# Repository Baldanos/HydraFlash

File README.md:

# Hydrabus NAND Flash shield

This shield uses the template made by Antti Nykänen <aon@umetronics.com>

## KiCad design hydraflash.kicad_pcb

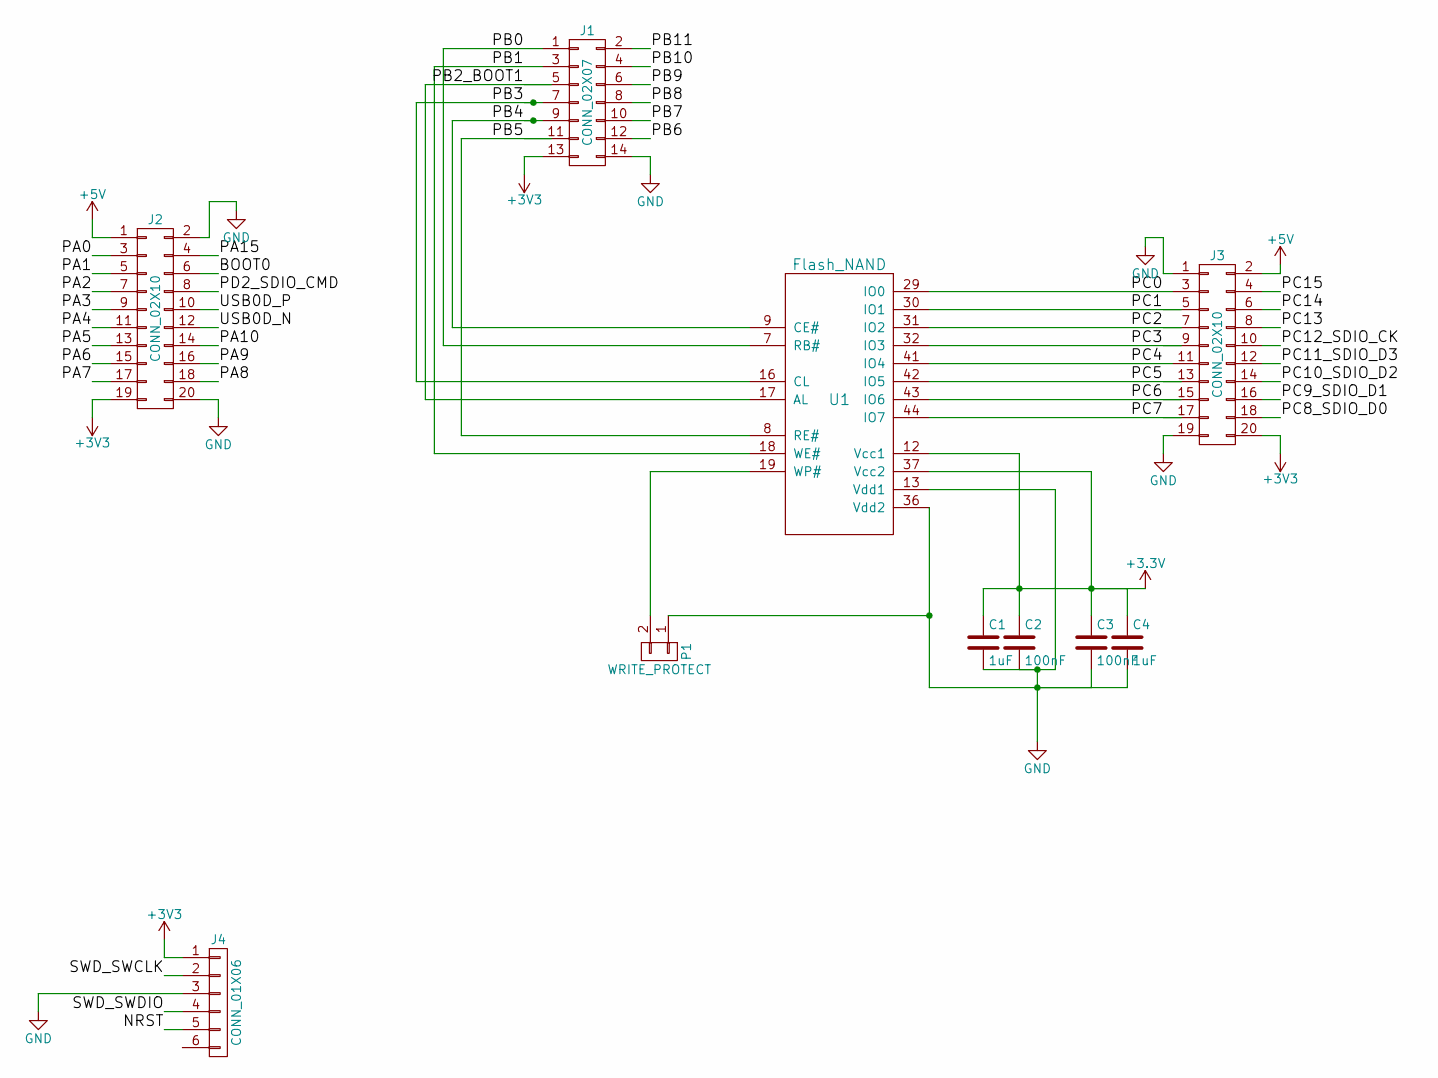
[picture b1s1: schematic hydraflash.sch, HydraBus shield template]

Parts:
C1, C4: 1uF; C_0805_HandSoldering
C2, C3: 100nF; C_0805_HandSoldering
J1: CONN_02X07; Hydrabus_Shield_Conn_2x07
J2, J3: CONN_02X10; Hydrabus_Shield_Conn_2x10
J4: CONN_01X06; Hydrabus_Shield_Conn_1x06
P1: WRITE_PROTECT; Pin_Header_Straight_1x02
U1: Flash_NAND; TSOP48ZIF

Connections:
+5V: J2.1, J3.2
/BOOT0: J2.6
/NRST: J4.5
/PA0: J2.3
/PA1: J2.5
/PA2: J2.7
/PA3: J2.9
/PA4: J2.11
/PA5: J2.13
/PA6: J2.15
/PA7: J2.17
/PA8: J2.18
/PA9: J2.16
/PA10: J2.14
/PA15: J2.4
/PB0: J1.1, U1.7 (RB#)
/PB1: J1.3, U1.18 (WE#)
/PB2_BOOT1: J1.5, U1.17 (AL)
/PB3: J1.7, U1.16 (CL)
/PB4: J1.9, U1.9 (CE#)
/PB5: J1.11, U1.8 (RE#)
/PB6: J1.12
/PB7: J1.10
/PB8: J1.8
/PB9: J1.6
/PB10: J1.4
/PB11: J1.2
/PC0: J3.3, U1.29 (IO0)
/PC1: J3.5, U1.30 (IO1)
/PC2: J3.7, U1.31 (IO2)
/PC3: J3.9, U1.32 (IO3)
/PC4: J3.11, U1.41 (IO4)
/PC5: J3.13, U1.42 (IO5)
/PC6: J3.15, U1.43 (IO6)
/PC7: J3.17, U1.44 (IO7)
/PC8_SDIO_D0: J3.18
/PC9_SDIO_D1: J3.16
/PC10_SDIO_D2: J3.14
/PC11_SDIO_D3: J3.12
/PC12_SDIO_CK: J3.10
/PC13: J3.8
/PC14: J3.6
/PC15: J3.4
/PD2_SDIO_CMD: J2.8
/SWD_SWCLK: J4.2
/SWD_SWDIO: J4.4
/USB0D_N: J2.12
/USB0D_P: J2.10
GND: C1.2, C2.2, C3.2, C4.2, J1.14, J2.2, J2.20, J3.1, J3.19, J4.3, P1.1, U1.13 (Vdd1), U1.36 (Vdd2)
unnamed: P1.2, U1.19 (WP#)

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
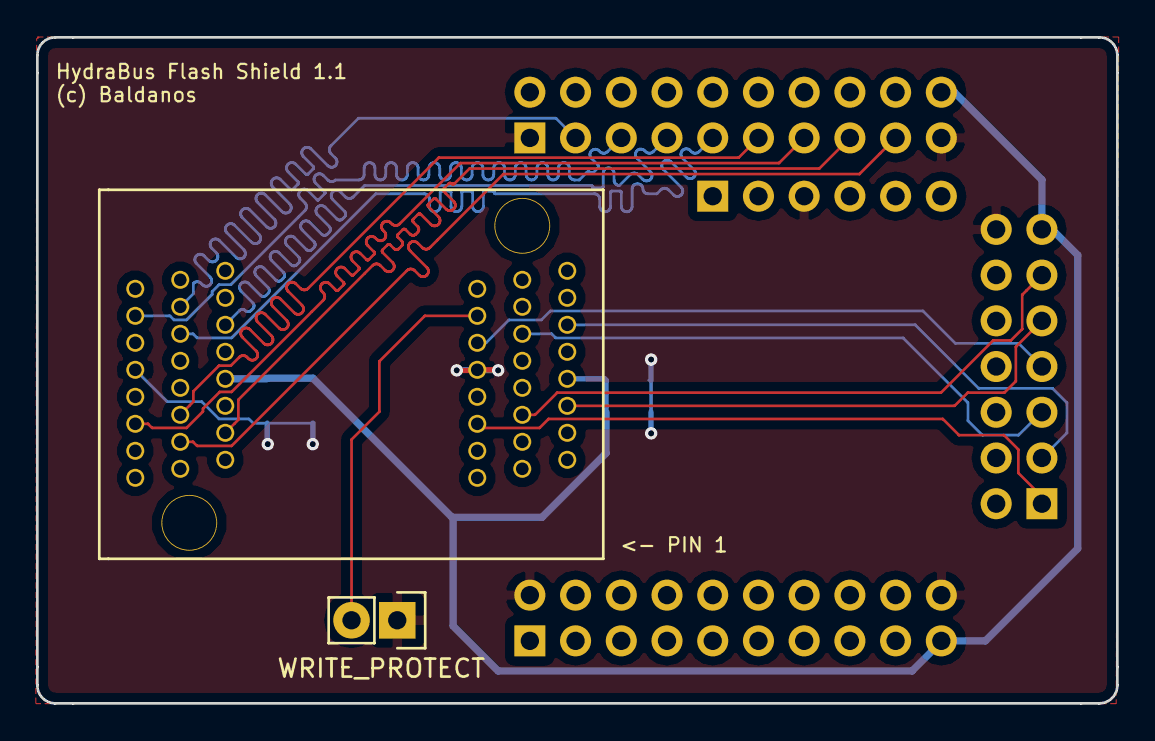
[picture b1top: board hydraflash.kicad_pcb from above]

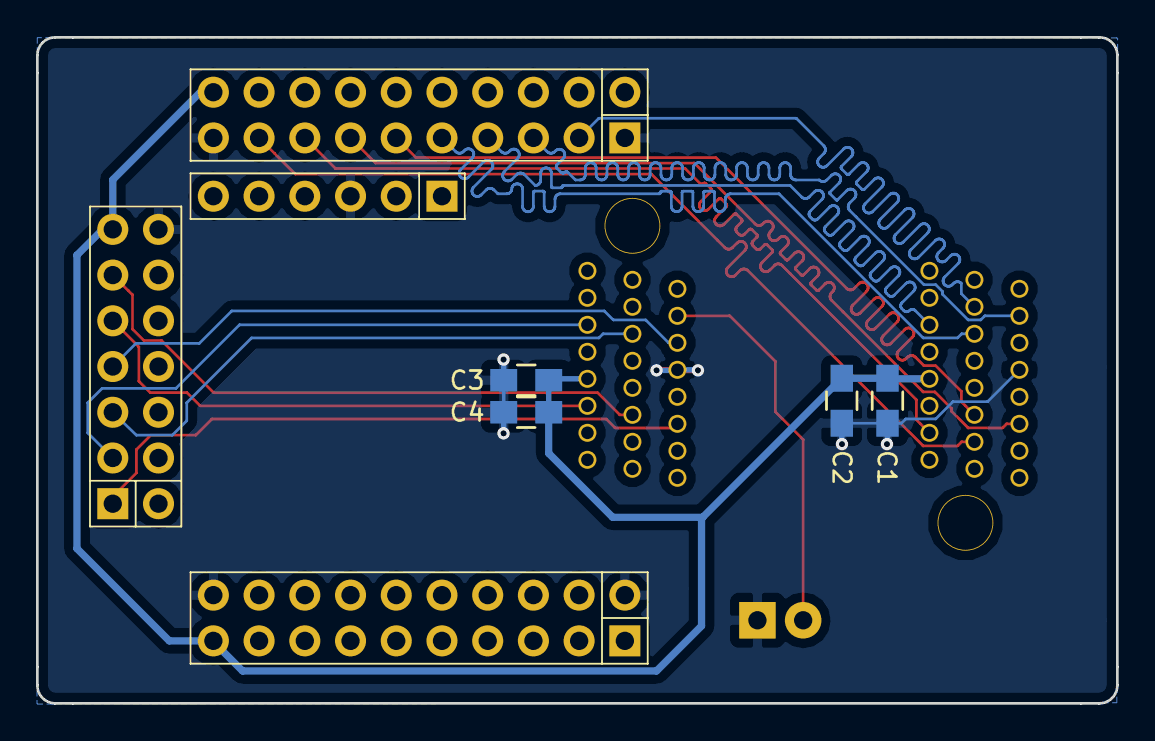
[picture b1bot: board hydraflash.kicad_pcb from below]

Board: 2 copper layers, 60.0 x 37.0 mm, 10 parts (8 on the bottom side), 18 nets.

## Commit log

2017-06-15 Routing improvements by bvernoux
2017-08-06 Minor update(Capacitor values and 3V3 routing with bigger wire)
2017-08-06 Add Gerber Files
2017-08-06 Add BOM

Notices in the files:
hydraflash.kicad_pcb:
CC BY-SA 4.0
